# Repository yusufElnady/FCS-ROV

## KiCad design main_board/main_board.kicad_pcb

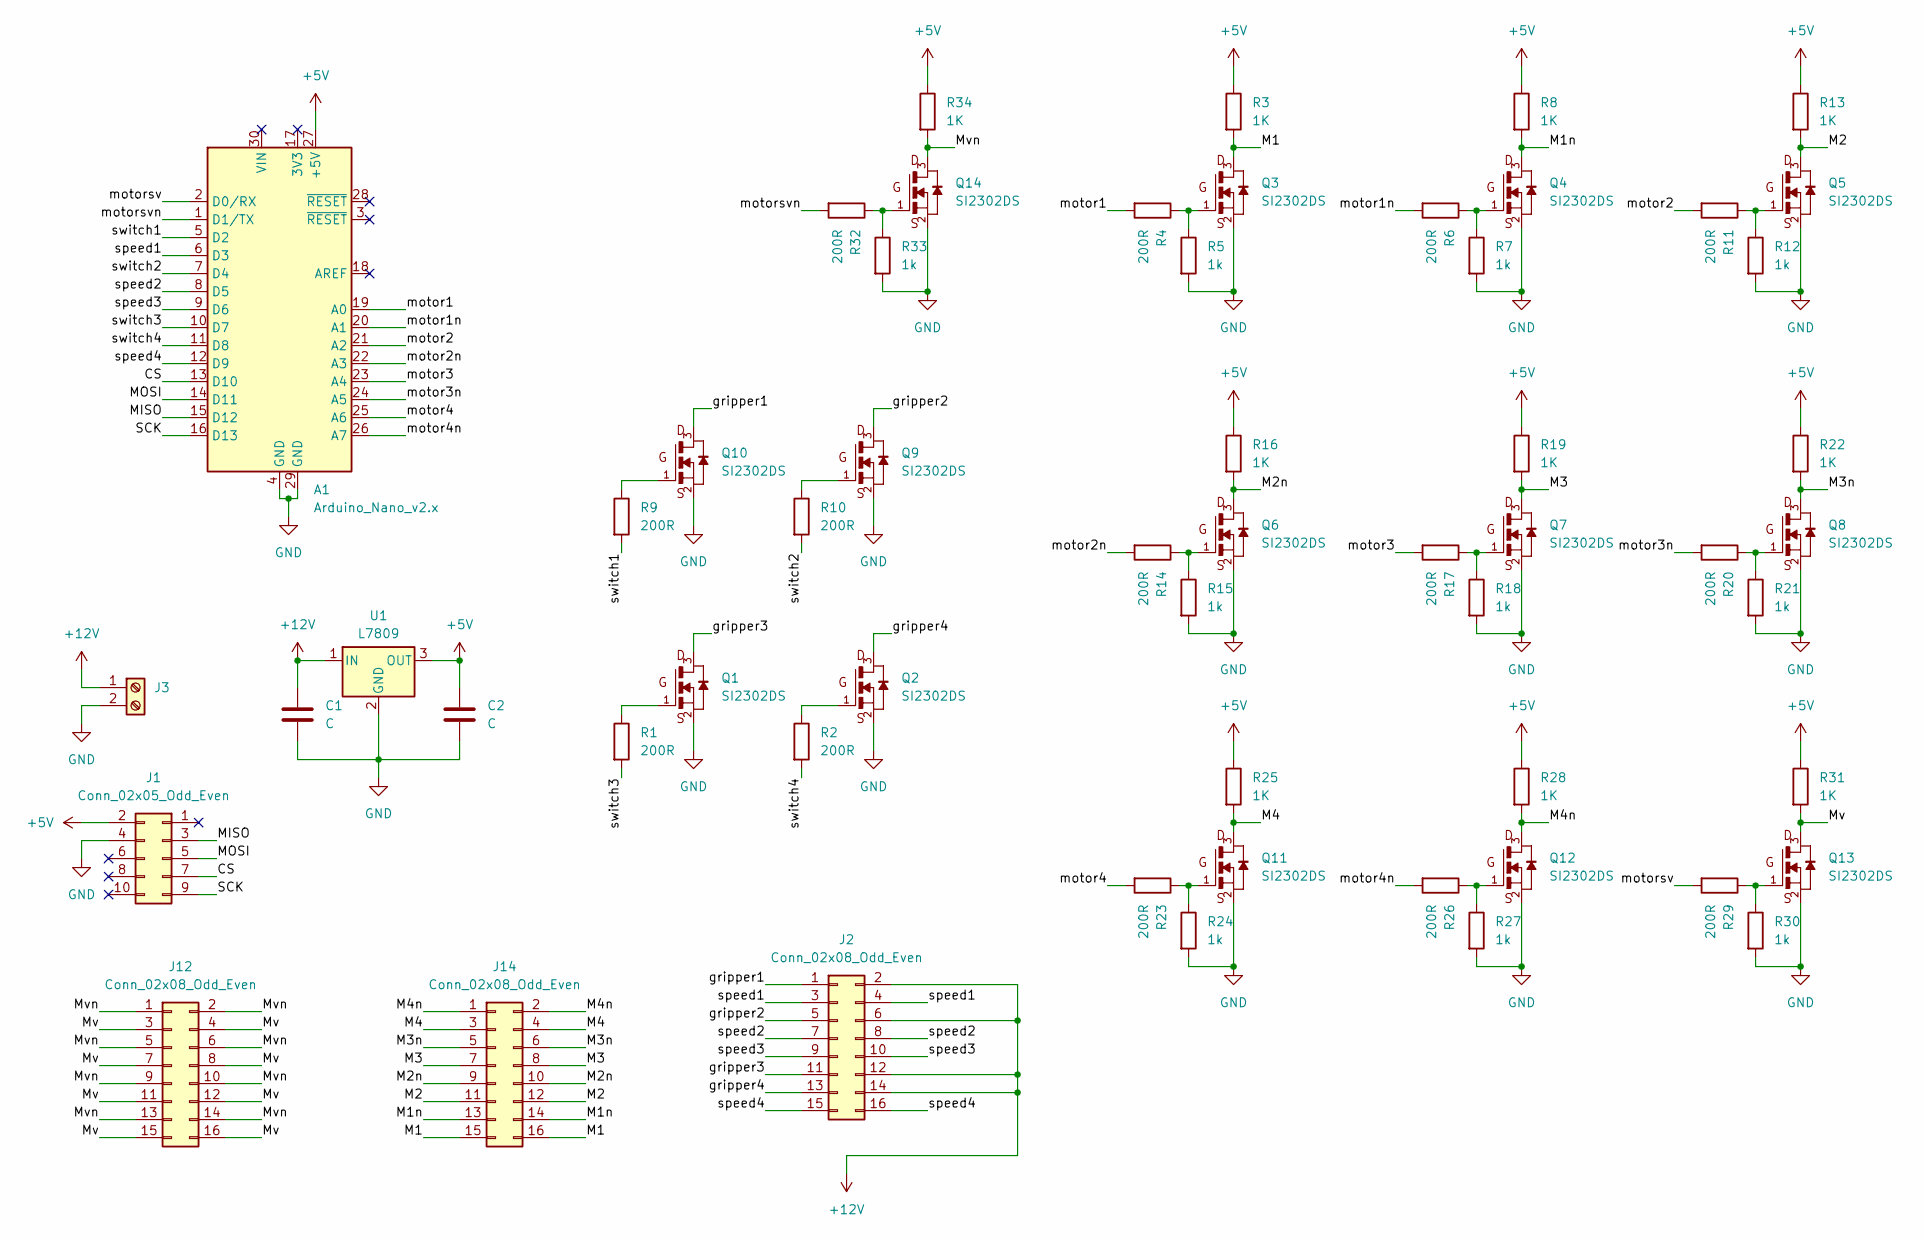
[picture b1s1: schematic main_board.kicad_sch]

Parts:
A1: Arduino_Nano_v2.x; Arduino_Nano
C1, C2: C; C_Disc_D4.3mm_W1.9mm_P5.00mm
J1: Conn_02x05_Odd_Even; PinSocket_2x05_P2.54mm_Vertical
J2, J12, J14: Conn_02x08_Odd_Even; PinSocket_2x08_P2.54mm_Vertical
J3: Screw_Terminal_01x02; TerminalBlock_bornier-2_P5.08mm
Q1, Q2, Q3, Q4, Q5, Q6, Q7, Q8, Q9, Q10, Q11, Q12, Q13, Q14: SI2302DS; SOT23-3_TO-236AB
R1, R2, R4, R6, R9, R10, R11, R14, R17, R20, R23, R26, R29, R32: 200R; R_0805_2012Metric
R3, R8, R13, R16, R19, R22, R25, R28, R31, R34: 1K; R_0805_2012Metric
R5, R7, R12, R15, R18, R21, R24, R27, R30, R33: 1k; R_0805_2012Metric
U1: L7809; TO220V

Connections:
+5V: A1.27 (+5V), C2.1, J1.2, R3.1, R8.1, R13.1, R16.1, R19.1, R22.1, R25.1, R28.1, R31.1, R34.1, U1.3 (OUT)
+12V: C1.1, J2.2, J2.6, J2.12, J2.14, J3.1, U1.1 (IN)
/CS: A1.13 (D10), J1.7
/M1: J14.15, J14.16, Q3.3, R3.2
/M1n: J14.13, J14.14, Q4.3, R8.2
/M2: J14.11, J14.12, Q5.3, R13.2
/M2n: J14.9, J14.10, Q6.3, R16.2
/M3: J14.7, J14.8, Q7.3, R19.2
/M3n: J14.5, J14.6, Q8.3, R22.2
/M4: J14.3, J14.4, Q11.3, R25.2
/M4n: J14.1, J14.2, Q12.3, R28.2
/MISO: A1.15 (D12), J1.3
/MOSI: A1.14 (D11), J1.5
/Mv: J12.3, J12.4, J12.7, J12.8, J12.11, J12.12, J12.15, J12.16, Q13.3, R31.2
/Mvn: J12.1, J12.2, J12.5, J12.6, J12.9, J12.10, J12.13, J12.14, Q14.3, R34.2
/SCK: A1.16 (D13), J1.9
/gripper1: J2.1, Q10.3
/gripper2: J2.5, Q9.3
/gripper3: J2.11, Q1.3
/gripper4: J2.13, Q2.3
/motor1: A1.19 (A0), R4.2
/motor1n: A1.20 (A1), R6.2
/motor2: A1.21 (A2), R11.2
/motor2n: A1.22 (A3), R14.2
/motor3: A1.23 (A4), R17.2
/motor3n: A1.24 (A5), R20.2
/motor4: A1.25 (A6), R23.2
/motor4n: A1.26 (A7), R26.2
/motorsv: A1.2 (D0/RX), R29.2
/motorsvn: A1.1 (D1/TX), R32.2
/speed1: A1.6 (D3), J2.3, J2.4
/speed2: A1.8 (D5), J2.7, J2.8
/speed3: A1.9 (D6), J2.9, J2.10
/speed4: A1.12 (D9), J2.15, J2.16
/switch1: A1.5 (D2), R9.2
/switch2: A1.7 (D4), R10.2
/switch3: A1.10 (D7), R1.2
/switch4: A1.11 (D8), R2.2
GND: A1.4 (GND), A1.29 (GND), C1.2, C2.2, J1.4, J3.2, Q1.2, Q2.2, Q3.2, Q4.2, Q5.2, Q6.2, Q7.2, Q8.2, Q9.2, Q10.2, Q11.2, Q12.2, Q13.2, Q14.2, R5.2, R7.2, R12.2, R15.2, R18.2, R21.2, R24.2, R27.2, R30.2, R33.2, U1.2 (GND)
unnamed: Q1.1, R1.1
unnamed: Q2.1, R2.1
unnamed: Q3.1, R4.1, R5.1
unnamed: Q4.1, R6.1, R7.1
unnamed: Q5.1, R11.1, R12.1
unnamed: Q6.1, R14.1, R15.1
unnamed: Q7.1, R17.1, R18.1
unnamed: Q8.1, R20.1, R21.1
unnamed: Q9.1, R10.1
unnamed: Q10.1, R9.1
unnamed: Q11.1, R23.1, R24.1
unnamed: Q12.1, R26.1, R27.1
unnamed: Q13.1, R29.1, R30.1
unnamed: Q14.1, R32.1, R33.1

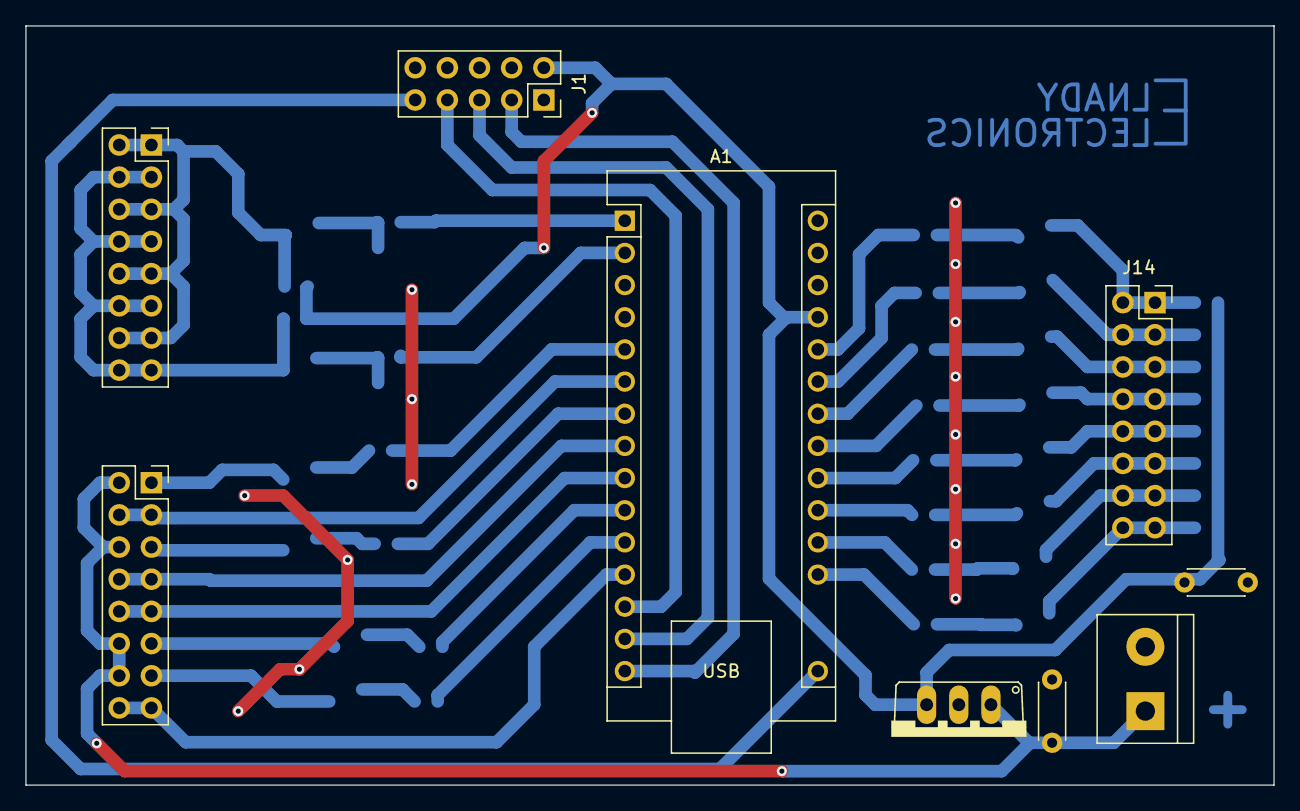
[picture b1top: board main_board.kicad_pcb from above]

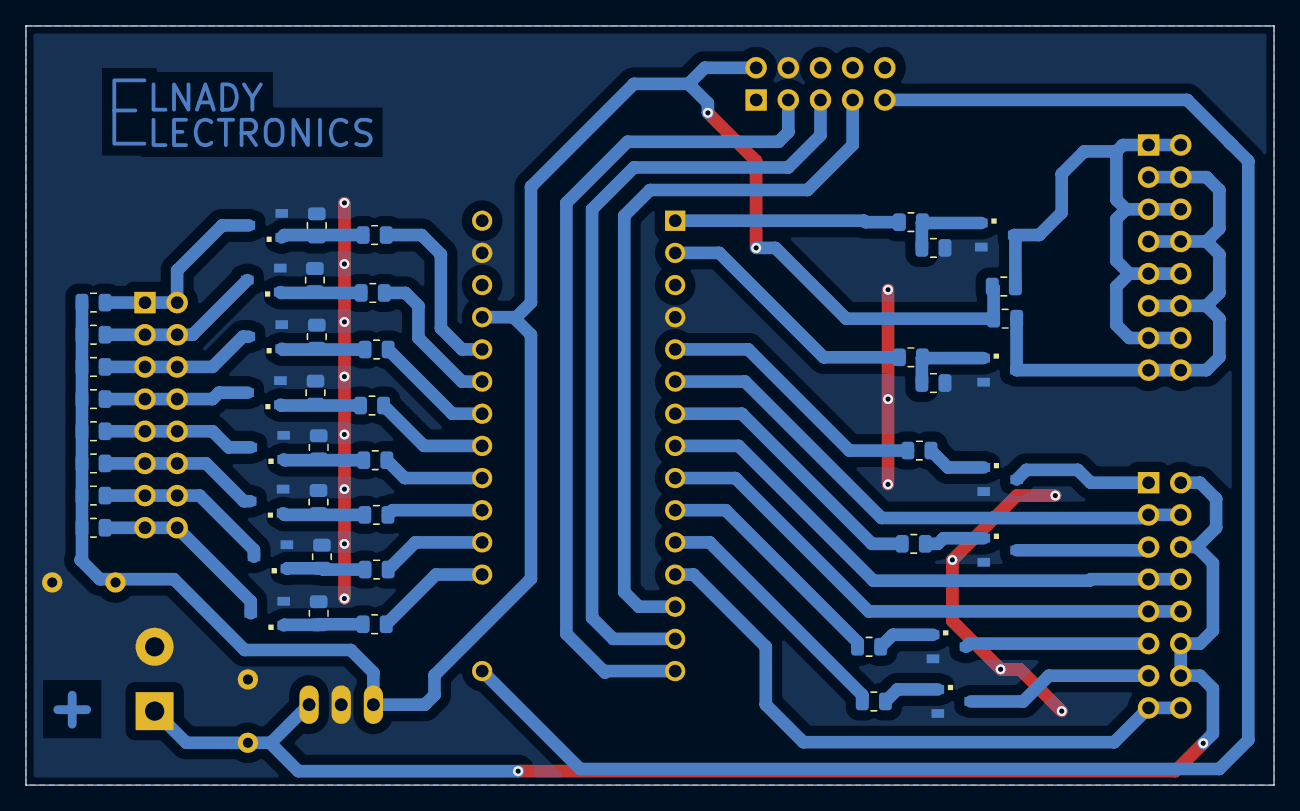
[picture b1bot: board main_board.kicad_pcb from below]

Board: 2 copper layers, 98.6 x 59.9 mm, 57 parts (48 on the bottom side), 53 nets.

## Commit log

2024-05-22 uploaded code pre-osama & the PCB design
2024-05-24 final adjustments
2024-05-24 fixed some indeces
